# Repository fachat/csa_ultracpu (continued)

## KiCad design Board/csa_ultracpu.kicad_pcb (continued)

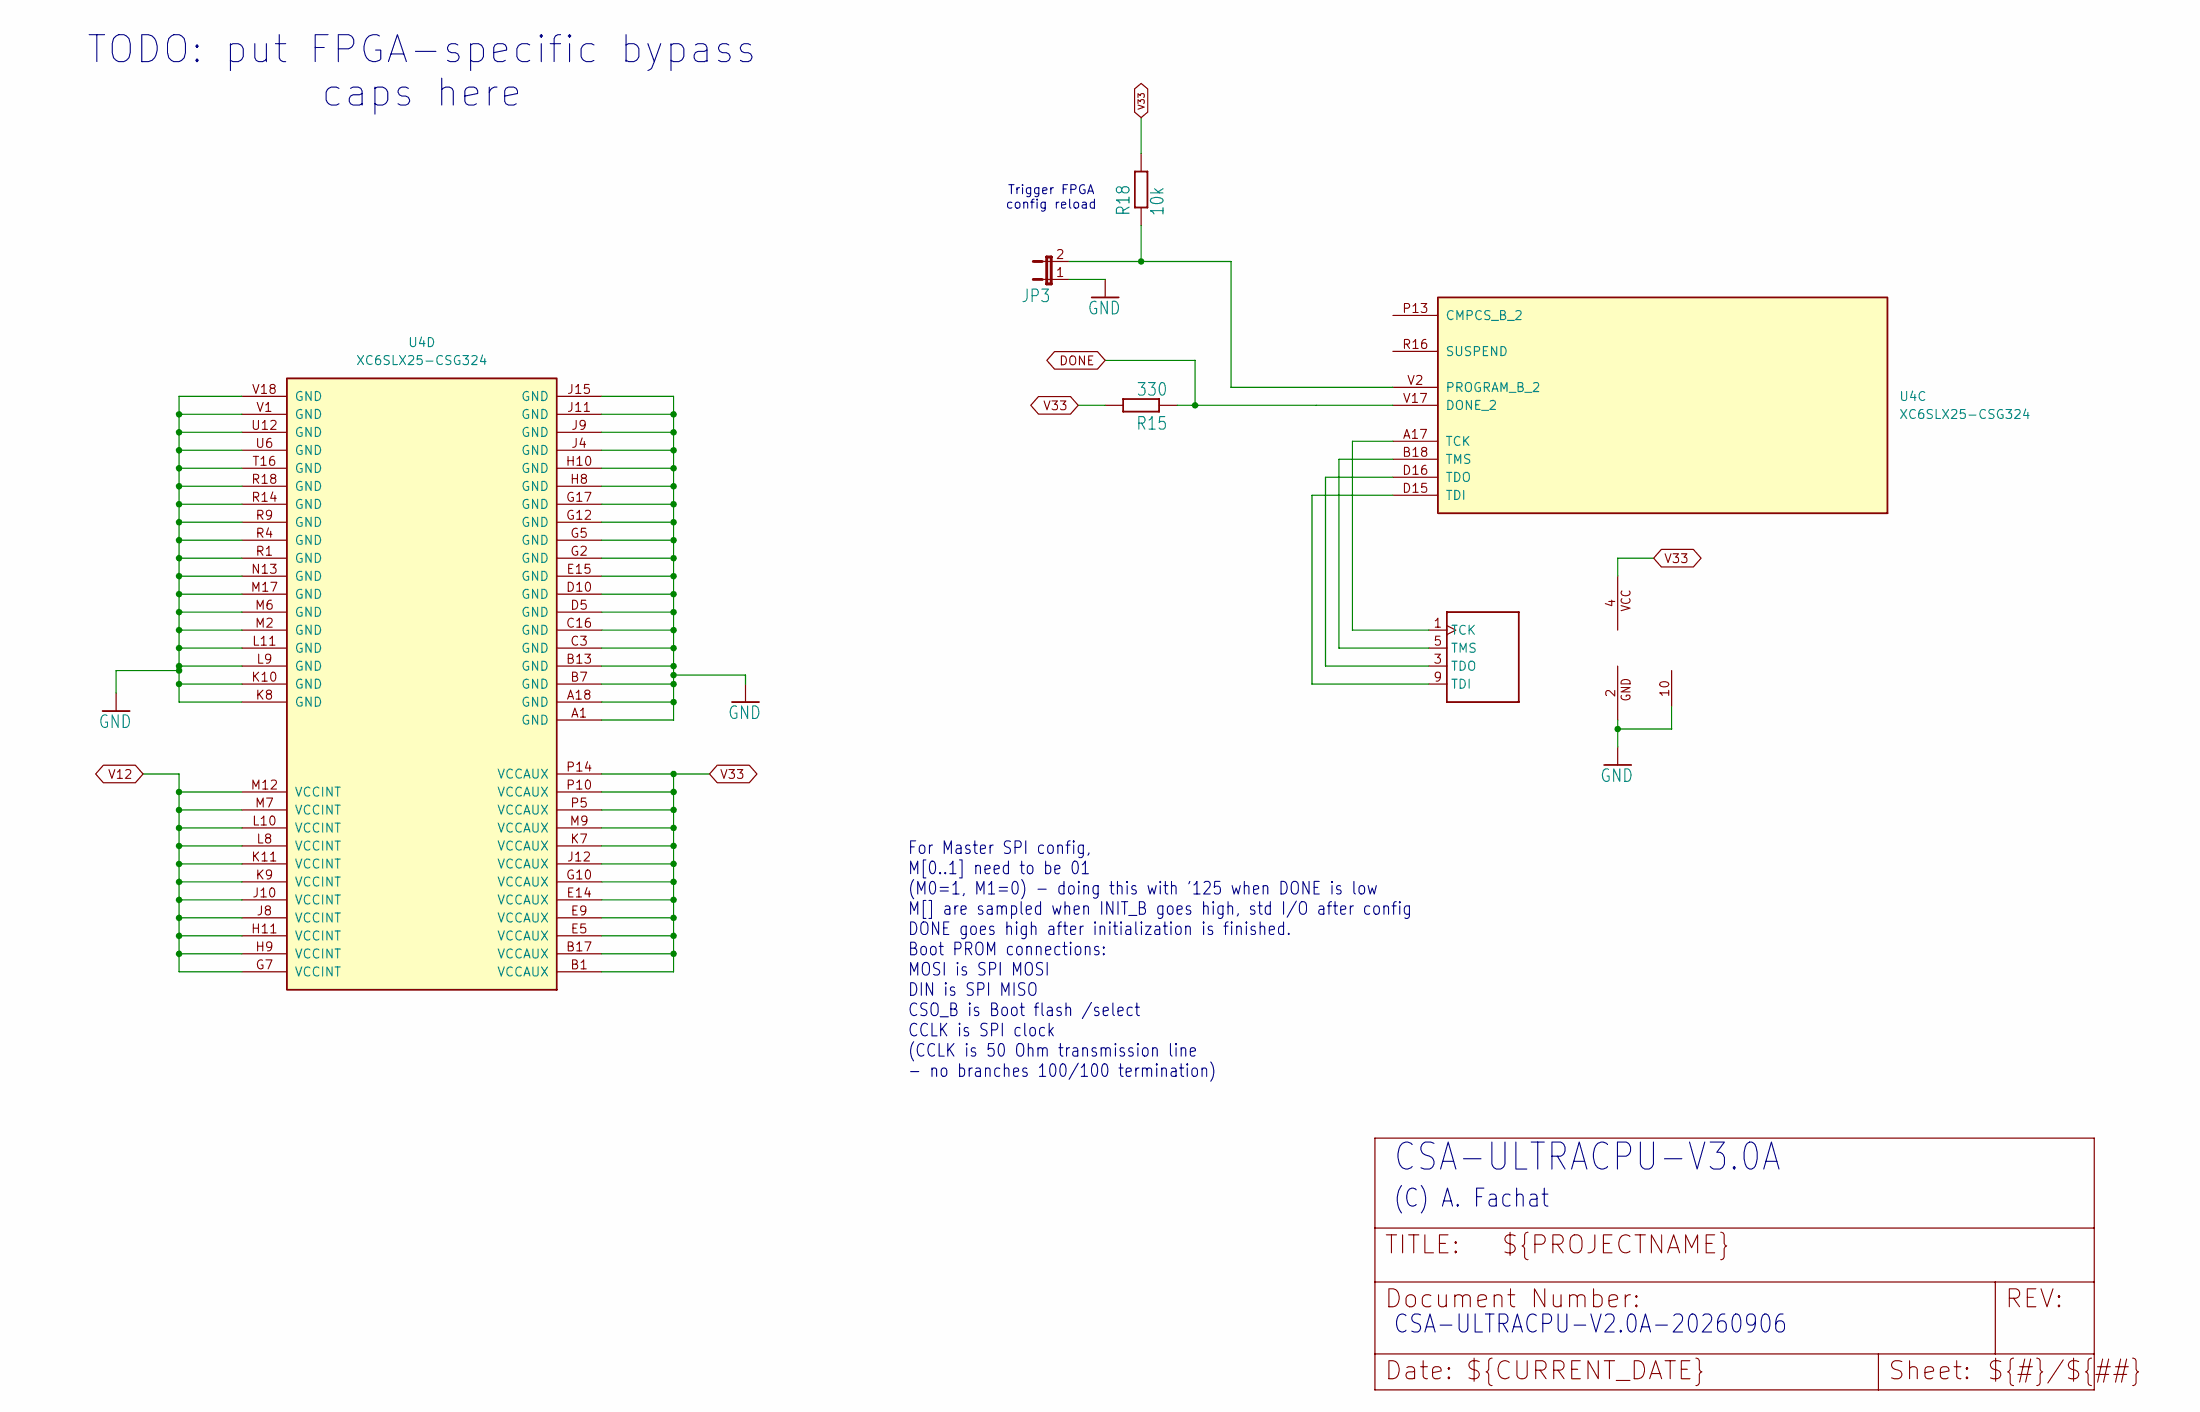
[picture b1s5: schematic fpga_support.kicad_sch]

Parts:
JP3: JP1E; JP1; LCSC C234182
R15: 330; C_0603_1608Metric_Pad1.08x0.95mm_HandSolder; LCSC C23138
R18: 10k; R_0805_2012Metric_Pad1.20x1.40mm_HandSolder; LCSC C17414
U4: XC6SLX25-CSG324; Xilinx_CSG324; LCSC C169795
U$2: XILINXPROG; FLAT10BOX; LCSC C5665

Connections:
DONE: R15.1, U4.V17 (DONE_2); also elsewhere on the board
GND: JP3.1, U4.A1 (GND), U4.A18 (GND), U4.B7 (GND), U4.B13 (GND), U4.C3 (GND), U4.C16 (GND), U4.D5 (GND), U4.D10 (GND), U4.E15 (GND), U4.G2 (GND), U4.G5 (GND), U4.G12 (GND), U4.G17 (GND), U4.H8 (GND), U4.H10 (GND), U4.J4 (GND), U4.J9 (GND), U4.J11 (GND), U4.J15 (GND), U4.K8 (GND), U4.K10 (GND), U4.L9 (GND), U4.L11 (GND), U4.M2 (GND), U4.M6 (GND), U4.M17 (GND), U4.N13 (GND), U4.R1 (GND), U4.R4 (GND), U4.R9 (GND), U4.R14 (GND), U4.R18 (GND), U4.T16 (GND), U4.U6 (GND), U4.U12 (GND), U4.V1 (GND), U4.V18 (GND), U$2.2 (GND), U$2.10; also elsewhere on the board
unnamed: JP3.2, R18.1, U4.V2 (PROGRAM_B_2)
unnamed: U4.A17 (TCK), U$2.1 (TCK)
unnamed: U4.D15 (TDI), U$2.9 (TDI)
unnamed: U4.D16 (TDO), U$2.3 (TDO)
unnamed: U4.B18 (TMS), U$2.5 (TMS)
V12: U4.G7 (VCCINT), U4.H9 (VCCINT), U4.H11 (VCCINT), U4.J8 (VCCINT), U4.J10 (VCCINT), U4.K9 (VCCINT), U4.K11 (VCCINT), U4.L8 (VCCINT), U4.L10 (VCCINT), U4.M7 (VCCINT), U4.M12 (VCCINT); also elsewhere on the board
V33: R15.2, R18.2, U4.B1 (VCCAUX), U4.B17 (VCCAUX), U4.E5 (VCCAUX), U4.E9 (VCCAUX), U4.E14 (VCCAUX), U4.G10 (VCCAUX), U4.J12 (VCCAUX), U4.K7 (VCCAUX), U4.M9 (VCCAUX), U4.P5 (VCCAUX), U4.P10 (VCCAUX), U4.P14 (VCCAUX), U$2.4 (VCC); also elsewhere on the board

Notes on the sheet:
For Master SPI config, M[0..1] need to be 01 (M0=1, M1=0) - doing this with '125 when DONE is low M[] are sampled when INIT_B goes high, std I/O after config DONE goes high after initialization is finished. Boot PROM connections: MOSI is SPI MOSI DIN is SPI MISO CSO_B is Boot flash /select CCLK is 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
CSA-ULTRACPU-V3.0A
TODO: put FPGA-specific bypass caps here
Trigger FPGA config reload
CSA-ULTRACPU-V2.0A-20260906
(C) A. Fachat

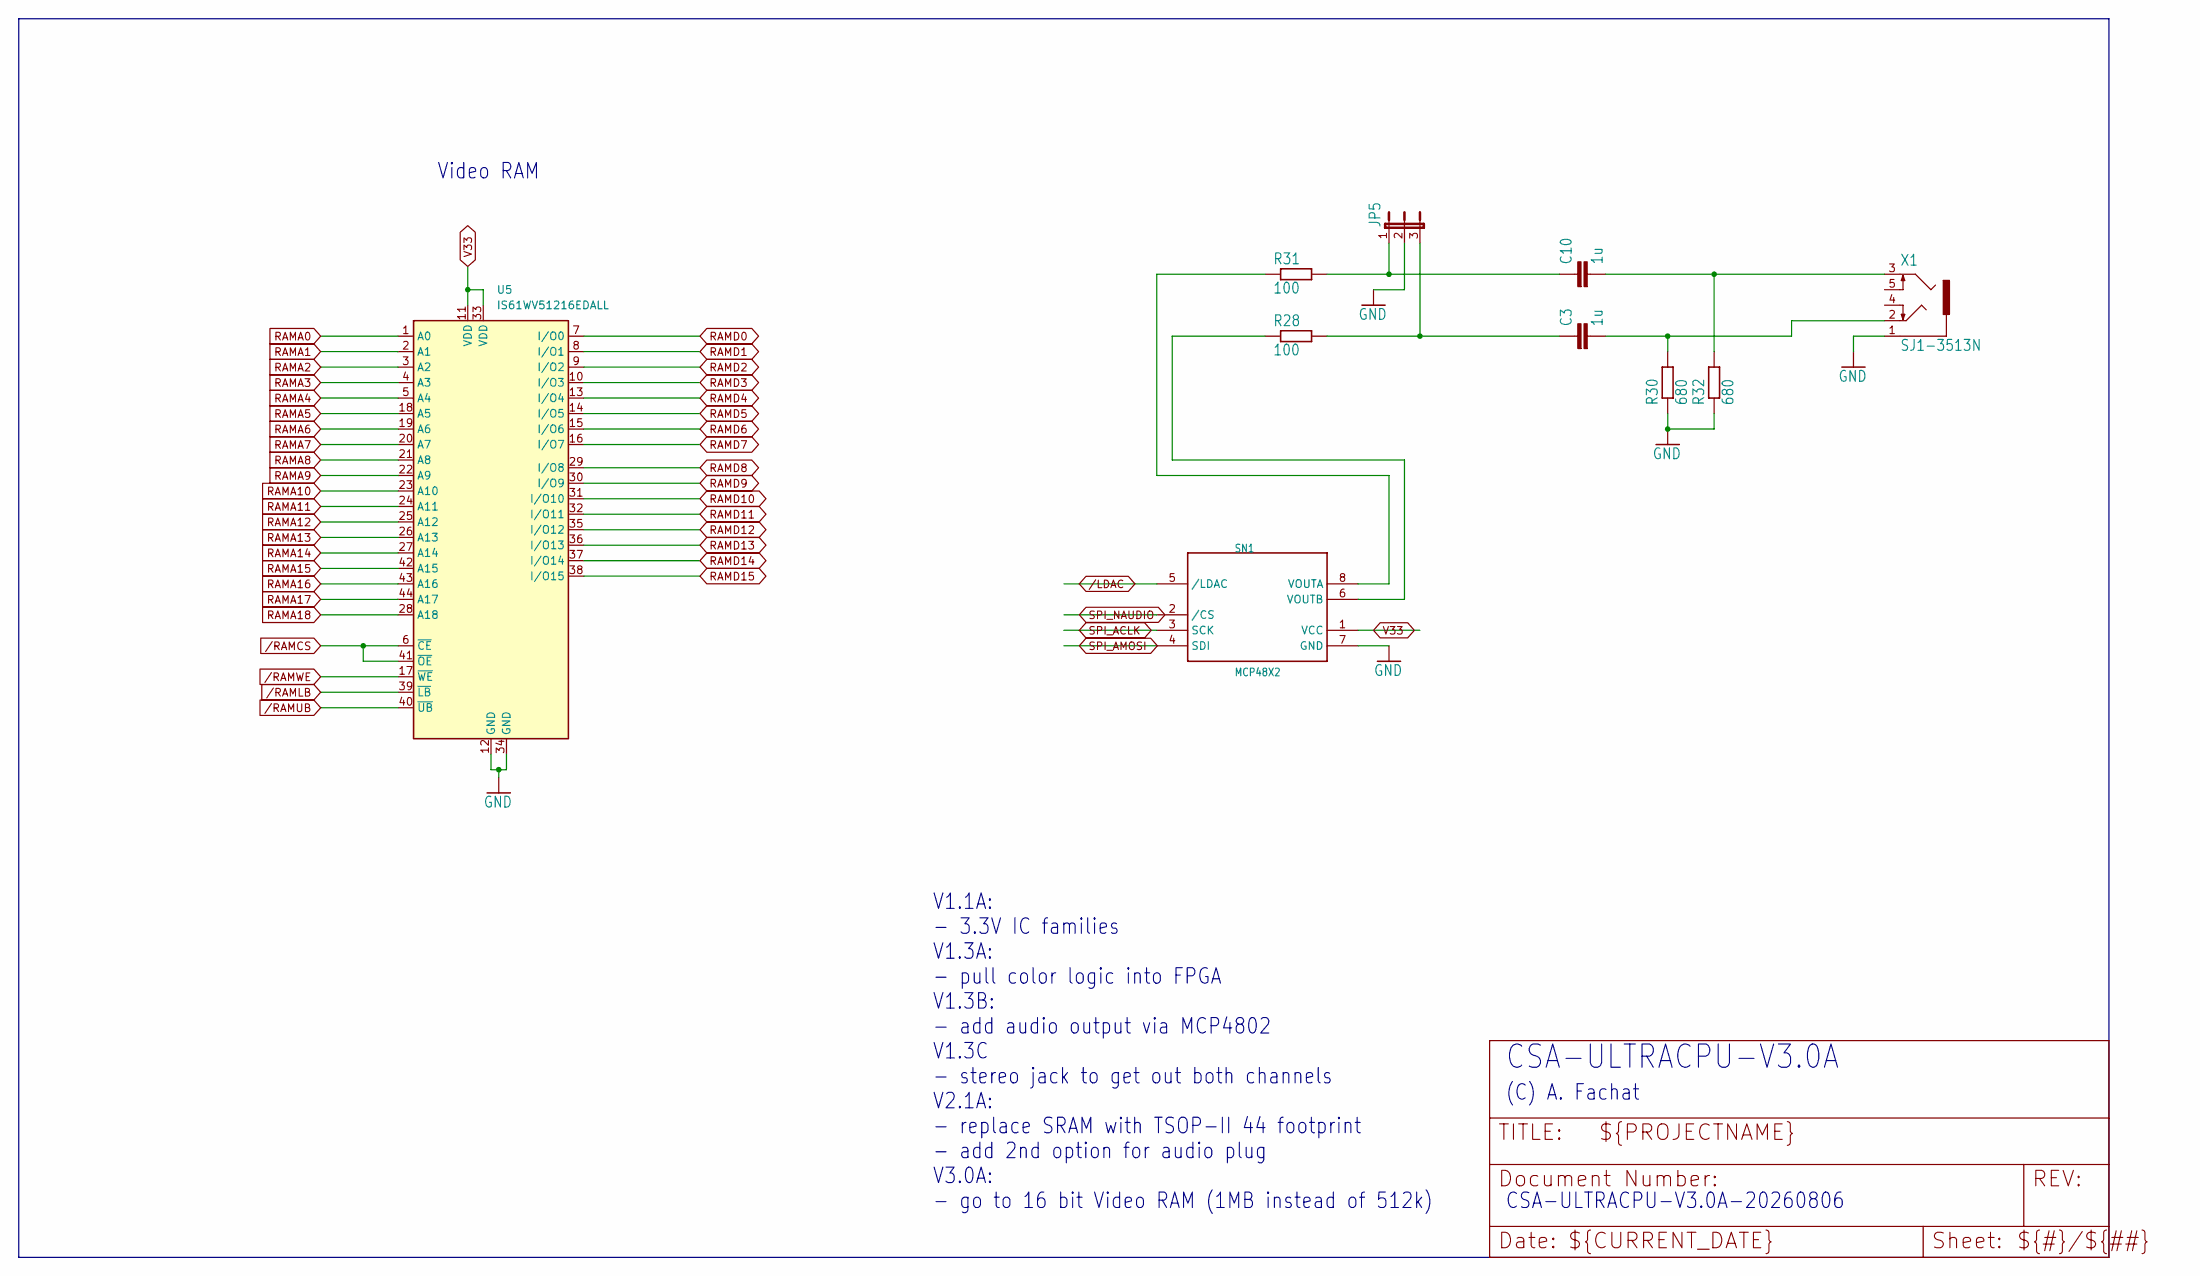
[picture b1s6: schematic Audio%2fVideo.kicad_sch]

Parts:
C3, C10: 1u; C_0603_1608Metric; LCSC C15849
JP5: JP2E; JP2; LCSC C587036
R28, R31: 100; R_0603_1608Metric_Pad0.98x0.95mm_HandSolder; LCSC C22775
R30, R32: 680; R_0603_1608Metric_Pad0.98x0.95mm_HandSolder; LCSC C23228
SN1: MCP48X2; SOIC8; LCSC C144363
U5: IS61WV51216EDALL; TSOP-II-44_10.16x18.41mm_P0.8mm; LCSC C57407
X1: SJ1-3513N; 1503_09; LCSC C145814

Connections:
GND: JP5.2, R30.1, R32.1, SN1.7 (GND), U5.12 (GND), U5.34 (GND), X1.1; also elsewhere on the board
unnamed: C3.1, JP5.3, R28.2
unnamed: C3.2, R30.2, X1.2
unnamed: C10.1, JP5.1, R31.2
unnamed: C10.2, R32.2, X1.3
unnamed: R31.1, SN1.8 (VOUTA)
unnamed: R28.1, SN1.6 (VOUTB)
RAMA0: U5.1 (A0); also elsewhere on the board
RAMA1: U5.2 (A1); also elsewhere on the board
RAMA2: U5.3 (A2); also elsewhere on the board
RAMA3: U5.4 (A3); also elsewhere on the board
RAMA4: U5.5 (A4); also elsewhere on the board
RAMA5: U5.18 (A5); also elsewhere on the board
RAMA6: U5.19 (A6); also elsewhere on the board
RAMA7: U5.20 (A7); also elsewhere on the board
RAMA8: U5.21 (A8); also elsewhere on the board
RAMA9: U5.22 (A9); also elsewhere on the board
RAMA10: U5.23 (A10); also elsewhere on the board
RAMA11: U5.24 (A11); also elsewhere on the board
RAMA12: U5.25 (A12); also elsewhere on the board
RAMA13: U5.26 (A13); also elsewhere on the board
RAMA14: U5.27 (A14); also elsewhere on the board
RAMA15: U5.42 (A15); also elsewhere on the board
RAMA16: U5.43 (A16); also elsewhere on the board
RAMA17: U5.44 (A17); also elsewhere on the board
RAMA18: U5.28 (A18); also elsewhere on the board
RAMD0: U5.7 (I/O0); also elsewhere on the board
RAMD1: U5.8 (I/O1); also elsewhere on the board
RAMD2: U5.9 (I/O2); also elsewhere on the board
RAMD3: U5.10 (I/O3); also elsewhere on the board
RAMD4: U5.13 (I/O4); also elsewhere on the board
RAMD5: U5.14 (I/O5); also elsewhere on the board
RAMD6: U5.15 (I/O6); also elsewhere on the board
RAMD7: U5.16 (I/O7); also elsewhere on the board
RAMD8: U5.29 (I/O8); also elsewhere on the board
RAMD9: U5.30 (I/O9); also elsewhere on the board
RAMD10: U5.31 (I/O10); also elsewhere on the board
RAMD11: U5.32 (I/O11); also elsewhere on the board
RAMD12: U5.35 (I/O12); also elsewhere on the board
RAMD13: U5.36 (I/O13); also elsewhere on the board
RAMD14: U5.37 (I/O14); also elsewhere on the board
RAMD15: U5.38 (I/O15); also elsewhere on the board
SPI_ACLK: SN1.3 (SCK); also elsewhere on the board
SPI_AMOSI: SN1.4 (SDI); also elsewhere on the board
SPI_NAUDIO: SN1.2 (/CS); also elsewhere on the board
V33: SN1.1 (VCC), U5.11 (VDD), U5.33 (VDD); also elsewhere on the board
/LDAC: SN1.5 (/LDAC); also elsewhere on the board
/RAMLB: U5.39 (~LB); also elsewhere on the board
/RAMUB: U5.40 (~UB); also elsewhere on the board

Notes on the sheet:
(C) A. Fachat
CSA-ULTRACPU-V3.0A-20260806
V1.1A: - 3.3V IC families V1.3A: - pull color logic into FPGA V1.3B: - add audio output via MCP4802 V1.3C - stereo jack to get out both channels V2.1A: - replace SRAM with TSOP-II 44 footprint - add 2nd option for audio plug V3.0A: - go to 16 bit Video RAM (1MB instead of 512k)
Video RAM
CSA-ULTRACPU-V3.0A

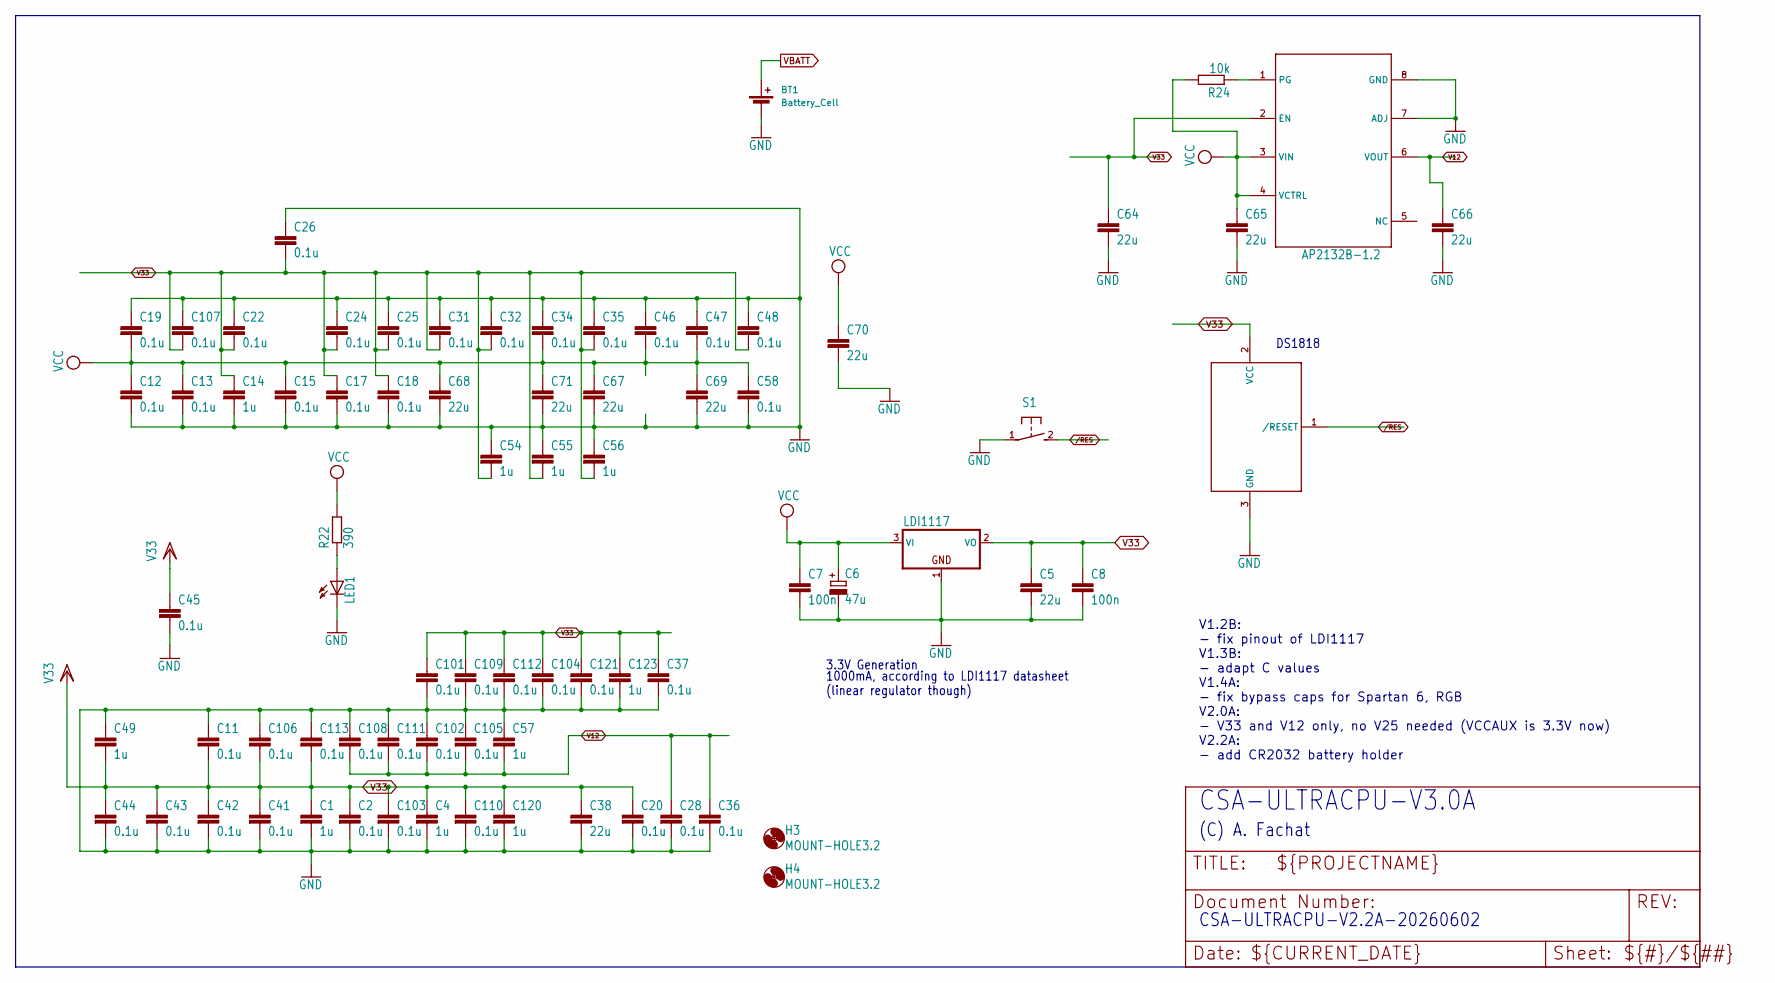
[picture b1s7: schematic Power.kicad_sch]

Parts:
BT1: Battery_Cell; Kinghelm CR2032 Holder; LCSC C5365915
C1, C4, C14, C49, C54, C55, C56, C57, C120, C123: 1u; C0603; LCSC C15849
C2, C11, C12, C13, C15, C17, C18, C19, C20, C22, C24, C25, C26, C28, C31, C32, C34, C35, C36, C37, C41, C42, C43, C44, C45, C46, C47, C48, C58, C101, C102, C103, C104, C105, C106, C107, C108, C109, C110, C111, C112, C113, C121: 0.1u; C0603; LCSC C14663
C5, C38, C64, C65, C66, C67, C68, C69, C70, C71: 22u; C0805; LCSC C45783
C6: 47u; C_0805_2012Metric_Pad1.18x1.45mm_HandSolder; LCSC C16780
C7, C8: 100n; C0603; LCSC C14663
DS1818: DS1818; SOT-23; LCSC C143298
H3, H4: MOUNT-HOLE3.2; 3,2
LED1: LED3MM; LCSC C85161
R22: 390; R_0603_1608Metric_Pad0.98x0.95mm_HandSolder; LCSC C23151
R24: 10k; R_0805_2012Metric_Pad1.20x1.40mm_HandSolder; LCSC C17414
S1: 31-XX; B3F-31XX; LCSC C231320
U$3: LDI1117; SOT223; LCSC C6186
U$16: AP2132B-1.2; PSOP-8-FIXED; LCSC C338874

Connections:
GND: BT1.2 (-), C1.2, C2.2, C4.2, C5.2, C6.2 (-), C7.2, C8.2, C11.1, C12.2, C13.2, C14.2, C15.2, C17.2, C18.2, C19.1, C20.2, C22.1, C24.1, C25.1, C26.1, C28.2, C31.1, C32.1, C34.1, C35.1, C36.2, C37.2, C38.2, C41.2, C42.2, C43.2, C44.2, C45.2, C46.1, C47.1, C48.1, C49.1, C54.1, C55.1, C56.1, C57.1, C58.2, C64.2, C65.2, C66.2, C67.2, C68.2, C69.2, C70.2, C71.2, C101.2, C102.1, C103.2, C104.2, C105.1, C106.1, C107.1, C108.1, C109.2, C110.2, C111.1, C112.2, C113.1, C120.2, C121.2, C123.2, DS1818.3 (GND), LED1.K (C), S1.1, U$3.1 (GND), U$16.7 (ADJ), U$16.8 (GND); also elsewhere on the board
unnamed: LED1.A, R22.1
unnamed: R24.1, U$16.1 (PG)
V12: C28.1, C36.1, C57.2, C66.1, C102.2, C105.2, C108.2, C111.2, U$16.6 (VOUT); also elsewhere on the board
V33: C1.1, C2.1, C4.1, C5.1, C8.1, C11.2, C14.1, C17.1, C18.1, C20.1, C22.2, C24.2, C25.2, C26.2, C31.2, C32.2, C35.2, C37.1, C38.1, C41.1, C42.1, C43.1, C44.1, C45.1, C48.2, C49.2, C54.2, C55.2, C56.2, C64.1, C101.1, C103.1, C104.1, C106.2, C107.2, C109.1, C110.1, C112.1, C113.2, C120.1, C121.1, C123.1, DS1818.2 (VCC), U$3.2 (VO), U$16.2 (EN); also elsewhere on the board
VBATT: BT1.1 (+); also elsewhere on the board
VCC: C6.1 (+), C7.1, C12.1, C13.1, C15.1, C19.2, C34.2, C46.2, C47.2, C58.1, C65.1, C67.1, C68.1, C69.1, C70.1, C71.1, R22.2, R24.2, U$3.3 (VI), U$16.3 (VIN), U$16.4 (VCTRL); also elsewhere on the board
/RES: DS1818.1 (/RESET), S1.2 (S); also elsewhere on the board

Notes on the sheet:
DS1818
(C) A. Fachat
CSA-ULTRACPU-V3.0A
1000mA, according to LDI1117 datasheet (linear regulator though)
CSA-ULTRACPU-V2.2A-20260602
3.3V Generation
V1.2B: - fix pinout of LDI1117 V1.3B: - adapt C values V1.4A: - fix bypass caps for Spartan 6, RGB V2.0A: - V33 and V12 only, no V25 needed (VCCAUX is 3.3V now) V2.2A: - add CR2032 battery holder

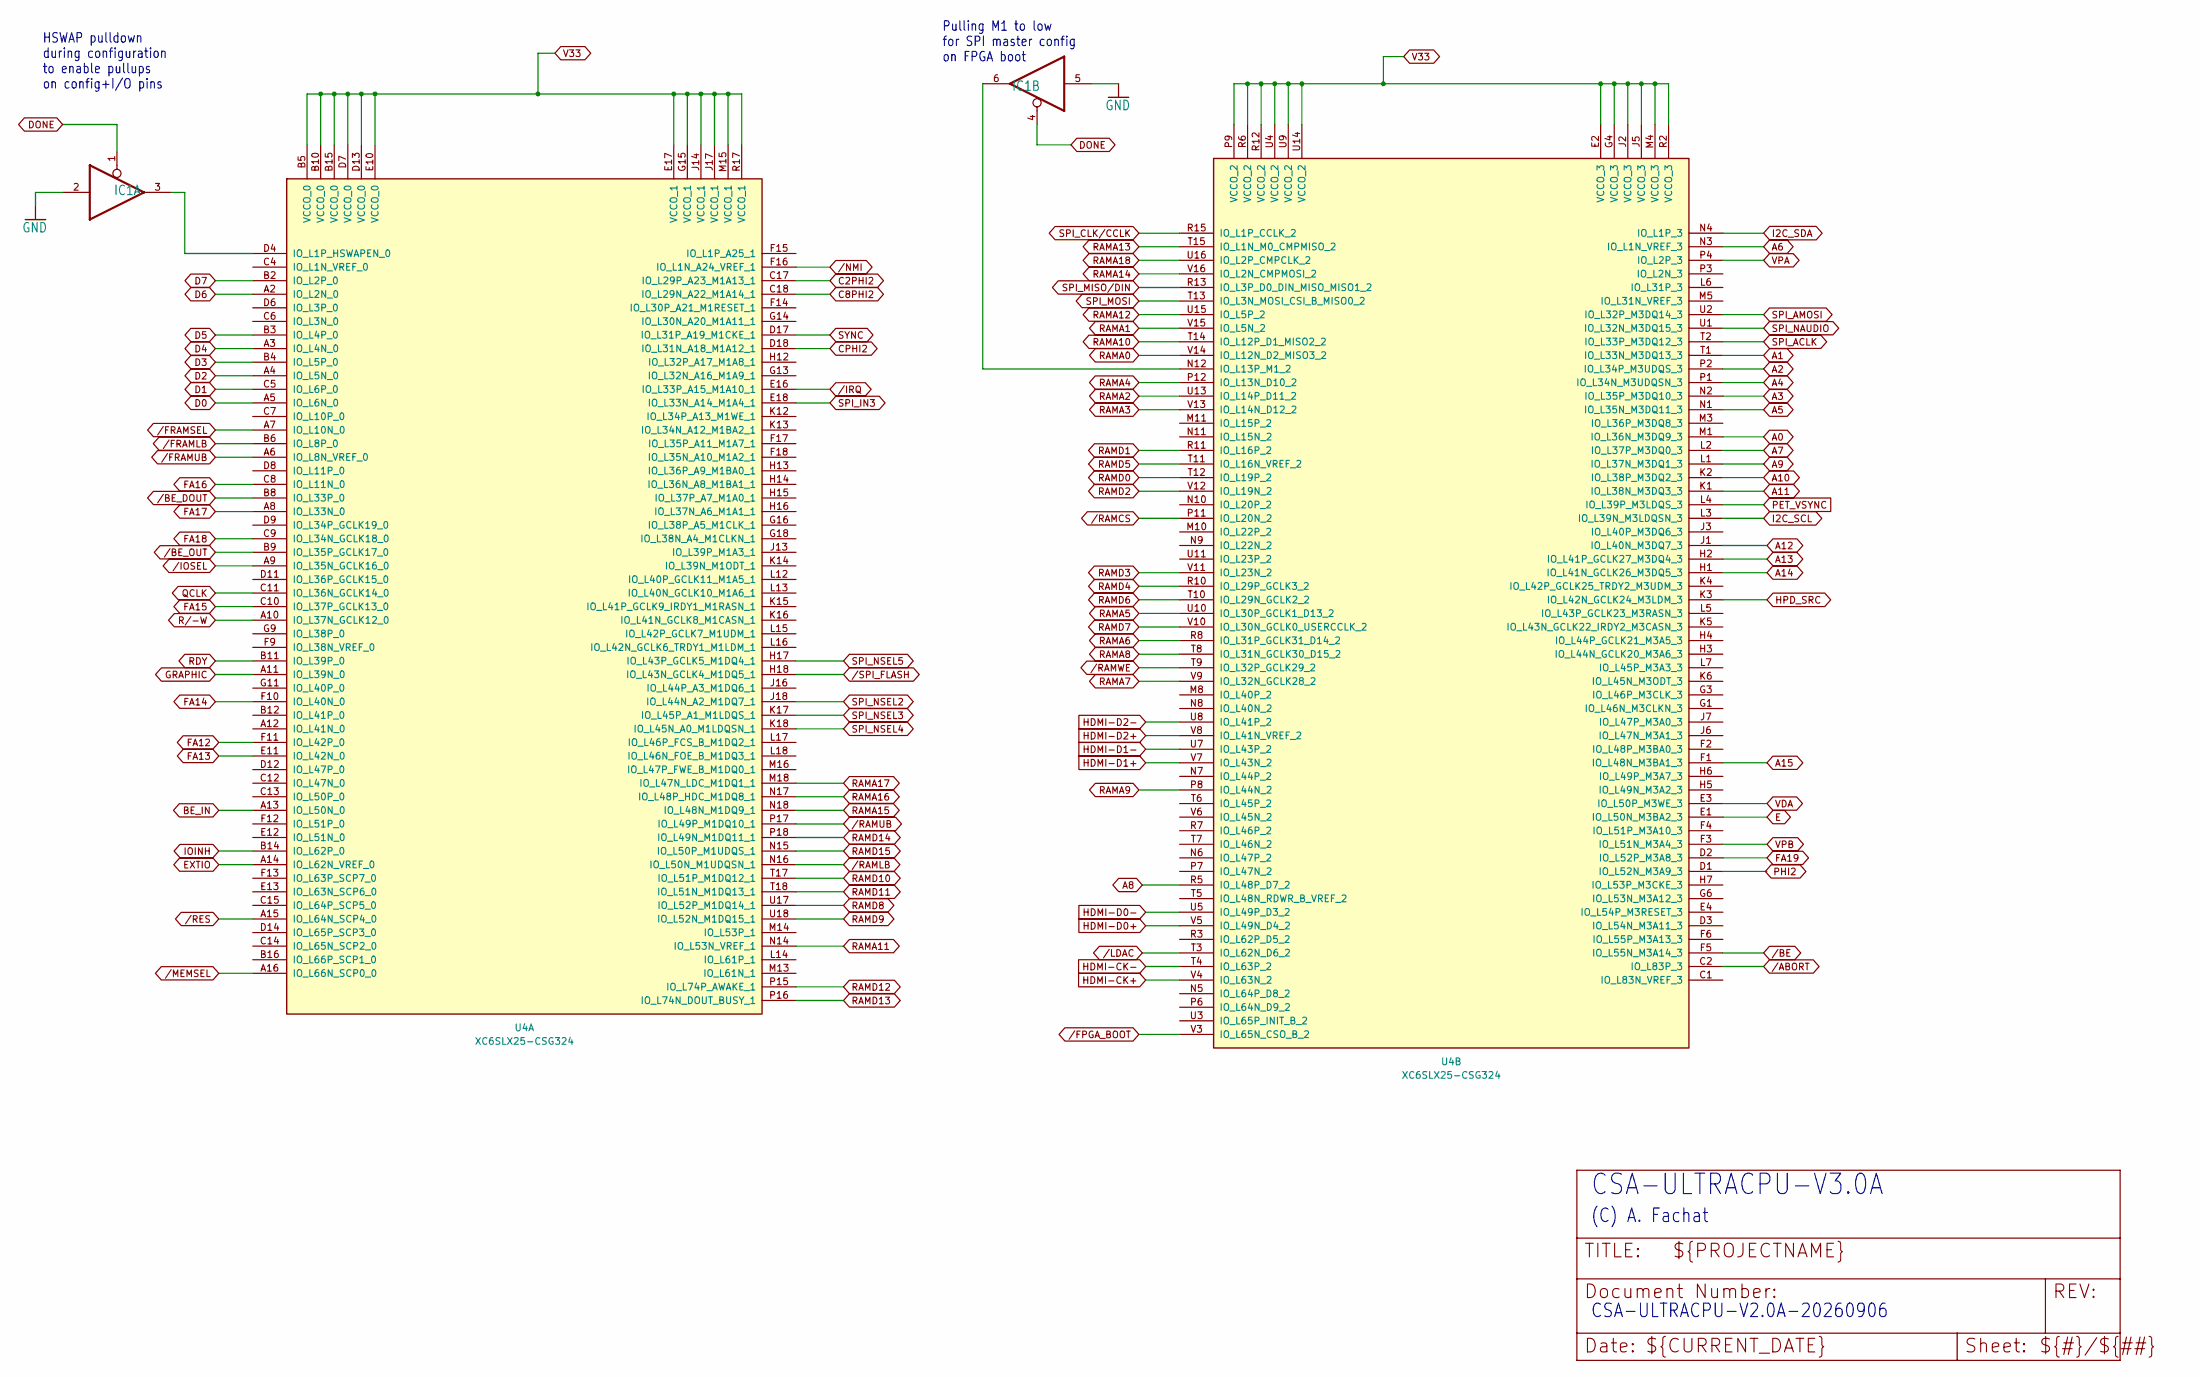
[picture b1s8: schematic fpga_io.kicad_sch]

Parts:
IC1: 74LVC125; SO14; LCSC C6057
U4: XC6SLX25-CSG324; Xilinx_CSG324; LCSC C169795

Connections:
A0: U4.M1 (IO_L36N_M3DQ9_3); also elsewhere on the board
A1: U4.T1 (IO_L33N_M3DQ13_3); also elsewhere on the board
A2: U4.P2 (IO_L34P_M3UDQS_3); also elsewhere on the board
A3: U4.N2 (IO_L35P_M3DQ10_3); also elsewhere on the board
A4: U4.P1 (IO_L34N_M3UDQSN_3); also elsewhere on the board
A5: U4.N1 (IO_L35N_M3DQ11_3); also elsewhere on the board
A6: U4.N3 (IO_L1N_VREF_3); also elsewhere on the board
A7: U4.L2 (IO_L37P_M3DQ0_3); also elsewhere on the board
A8: U4.R5 (IO_L48P_D7_2); also elsewhere on the board
A9: U4.L1 (IO_L37N_M3DQ1_3); also elsewhere on the board
A10: U4.K2 (IO_L38P_M3DQ2_3); also elsewhere on the board
A11: U4.K1 (IO_L38N_M3DQ3_3); also elsewhere on the board
A12: U4.J1 (IO_L40N_M3DQ7_3); also elsewhere on the board
A13: U4.H2 (IO_L41P_GCLK27_M3DQ4_3); also elsewhere on the board
A14: U4.H1 (IO_L41N_GCLK26_M3DQ5_3); also elsewhere on the board
A15: U4.F1 (IO_L48N_M3BA1_3); also elsewhere on the board
BE_IN: U4.A13 (IO_L50N_0); also elsewhere on the board
C2PHI2: U4.C17 (IO_L29P_A23_M1A13_1); also elsewhere on the board
C8PHI2: U4.C18 (IO_L29N_A22_M1A14_1); also elsewhere on the board
CPHI2: U4.D18 (IO_L31N_A18_M1A12_1); also elsewhere on the board
D0: U4.A5 (IO_L6N_0); also elsewhere on the board
D1: U4.C5 (IO_L6P_0); also elsewhere on the board
D2: U4.A4 (IO_L5N_0); also elsewhere on the board
D3: U4.B4 (IO_L5P_0); also elsewhere on the board
D4: U4.A3 (IO_L4N_0); also elsewhere on the board
D5: U4.B3 (IO_L4P_0); also elsewhere on the board
D6: U4.A2 (IO_L2N_0); also elsewhere on the board
D7: U4.B2 (IO_L2P_0); also elsewhere on the board
DONE: IC1.1 (OE), IC1.4 (OE); also elsewhere on the board
E: U4.E1 (IO_L50N_M3BA2_3); also elsewhere on the board
EXTIO: U4.A14 (IO_L62N_VREF_0); also elsewhere on the board
FA12: U4.F11 (IO_L42P_0); also elsewhere on the board
FA13: U4.E11 (IO_L42N_0); also elsewhere on the board
FA14: U4.F10 (IO_L40N_0); also elsewhere on the board
FA15: U4.C10 (IO_L37P_GCLK13_0); also elsewhere on the board
FA16: U4.C8 (IO_L11N_0); also elsewhere on the board
FA17: U4.A8 (IO_L33N_0); also elsewhere on the board
FA18: U4.C9 (IO_L34N_GCLK18_0); also elsewhere on the board
FA19: U4.D2 (IO_L52P_M3A8_3); also elsewhere on the board
GND: IC1.2 (I), IC1.5 (I); also elsewhere on the board
GRAPHIC: U4.A11 (IO_L39N_0); also elsewhere on the board
HDMI-CK+: U4.V4 (IO_L63N_2); also elsewhere on the board
HDMI-CK-: U4.T4 (IO_L63P_2); also elsewhere on the board
HDMI-D0+: U4.V5 (IO_L49N_D4_2); also elsewhere on the board
HDMI-D0-: U4.U5 (IO_L49P_D3_2); also elsewhere on the board
HDMI-D1+: U4.V7 (IO_L43N_2); also elsewhere on the board
HDMI-D1-: U4.U7 (IO_L43P_2); also elsewhere on the board
HDMI-D2+: U4.V8 (IO_L41N_VREF_2); also elsewhere on the board
HDMI-D2-: U4.U8 (IO_L41P_2); also elsewhere on the board
HPD_SRC: U4.K3 (IO_L42N_GCLK24_M3LDM_3); also elsewhere on the board
I2C_SCL: U4.L3 (IO_L39N_M3LDQSN_3); also elsewhere on the board
I2C_SDA: U4.N4 (IO_L1P_3); also elsewhere on the board
IOINH: U4.B14 (IO_L62P_0); also elsewhere on the board
unnamed: IC1.3 (O), U4.D4 (IO_L1P_HSWAPEN_0)
unnamed: IC1.6 (O), U4.N12 (IO_L13P_M1_2)
PET_VSYNC: U4.L4 (IO_L39P_M3LDQS_3); also elsewhere on the board
PHI2: U4.D1 (IO_L52N_M3A9_3); also elsewhere on the board
QCLK: U4.C11 (IO_L36N_GCLK14_0); also elsewhere on the board
RAMA0: U4.V14 (IO_L12N_D2_MISO3_2); also elsewhere on the board
RAMA1: U4.V15 (IO_L5N_2); also elsewhere on the board
RAMA2: U4.U13 (IO_L14P_D11_2); also elsewhere on the board
RAMA3: U4.V13 (IO_L14N_D12_2); also elsewhere on the board
RAMA4: U4.P12 (IO_L13N_D10_2); also elsewhere on the board
RAMA5: U4.U10 (IO_L30P_GCLK1_D13_2); also elsewhere on the board
RAMA6: U4.R8 (IO_L31P_GCLK31_D14_2); also elsewhere on the board
RAMA7: U4.V9 (IO_L32N_GCLK28_2); also elsewhere on the board
RAMA8: U4.T8 (IO_L31N_GCLK30_D15_2); also elsewhere on the board
RAMA9: U4.P8 (IO_L44N_2); also elsewhere on the board
RAMA10: U4.T14 (IO_L12P_D1_MISO2_2); also elsewhere on the board
RAMA11: U4.N14 (IO_L53N_VREF_1); also elsewhere on the board
RAMA12: U4.U15 (IO_L5P_2); also elsewhere on the board
RAMA13: U4.T15 (IO_L1N_M0_CMPMISO_2); also elsewhere on the board
RAMA14: U4.V16 (IO_L2N_CMPMOSI_2); also elsewhere on the board
RAMA15: U4.N18 (IO_L48N_M1DQ9_1); also elsewhere on the board
RAMA16: U4.N17 (IO_L48P_HDC_M1DQ8_1); also elsewhere on the board
RAMA17: U4.M18 (IO_L47N_LDC_M1DQ1_1); also elsewhere on the board
RAMA18: U4.U16 (IO_L2P_CMPCLK_2); also elsewhere on the board
RAMD0: U4.T12 (IO_L19P_2); also elsewhere on the board
RAMD1: U4.R11 (IO_L16P_2); also elsewhere on the board
RAMD2: U4.V12 (IO_L19N_2); also elsewhere on the board
RAMD3: U4.V11 (IO_L23N_2); also elsewhere on the board
RAMD4: U4.R10 (IO_L29P_GCLK3_2); also elsewhere on the board
RAMD5: U4.T11 (IO_L16N_VREF_2); also elsewhere on the board
RAMD6: U4.T10 (IO_L29N_GCLK2_2); also elsewhere on the board
RAMD7: U4.V10 (IO_L30N_GCLK0_USERCCLK_2); also elsewhere on the board
RAMD8: U4.U17 (IO_L52P_M1DQ14_1); also elsewhere on the board
RAMD9: U4.U18 (IO_L52N_M1DQ15_1); also elsewhere on the board
RAMD10: U4.T17 (IO_L51P_M1DQ12_1); also elsewhere on the board
RAMD11: U4.T18 (IO_L51N_M1DQ13_1); also elsewhere on the board
RAMD12: U4.P15 (IO_L74P_AWAKE_1); also elsewhere on the board
RAMD13: U4.P16 (IO_L74N_DOUT_BUSY_1); also elsewhere on the board
RAMD14: U4.P18 (IO_L49N_M1DQ11_1); also elsewhere on the board
RAMD15: U4.N15 (IO_L50P_M1UDQS_1); also elsewhere on the board
RDY: U4.B11 (IO_L39P_0); also elsewhere on the board
SPI_ACLK: U4.T2 (IO_L33P_M3DQ12_3); also elsewhere on the board
SPI_AMOSI: U4.U2 (IO_L32P_M3DQ14_3); also elsewhere on the board
SPI_CLK/CCLK: U4.R15 (IO_L1P_CCLK_2); also elsewhere on the board
SPI_IN3: U4.E18 (IO_L33N_A14_M1A4_1); also elsewhere on the board
SPI_MISO/DIN: U4.R13 (IO_L3P_D0_DIN_MISO_MISO1_2); also elsewhere on the board
SPI_MOSI: U4.T13 (IO_L3N_MOSI_CSI_B_MISO0_2); also elsewhere on the board
SPI_NAUDIO: U4.U1 (IO_L32N_M3DQ15_3); also elsewhere on the board
SPI_NSEL2: U4.J18 (IO_L44N_A2_M1DQ7_1); also elsewhere on the board
SPI_NSEL3: U4.K17 (IO_L45P_A1_M1LDQS_1); also elsewhere on the board
SPI_NSEL4: U4.K18 (IO_L45N_A0_M1LDQSN_1); also elsewhere on the board
SPI_NSEL5: U4.H17 (IO_L43P_GCLK5_M1DQ4_1); also elsewhere on the board
SYNC: U4.D17 (IO_L31P_A19_M1CKE_1); also elsewhere on the board
V33: U4.B5 (VCCO_0), U4.B10 (VCCO_0), U4.B15 (VCCO_0), U4.D7 (VCCO_0), U4.D13 (VCCO_0), U4.E2 (VCCO_3), U4.E10 (VCCO_0), U4.E17 (VCCO_1), U4.G4 (VCCO_3), U4.G15 (VCCO_1), U4.J2 (VCCO_3), U4.J5 (VCCO_3), U4.J14 (VCCO_1), U4.J17 (VCCO_1), U4.M4 (VCCO_3), U4.M15 (VCCO_1), U4.P9 (VCCO_2), U4.R2 (VCCO_3), U4.R6 (VCCO_2), U4.R12 (VCCO_2), U4.R17 (VCCO_1), U4.U4 (VCCO_2), U4.U9 (VCCO_2), U4.U14 (VCCO_2); also elsewhere on the board
VDA: U4.E3 (IO_L50P_M3WE_3); also elsewhere on the board
VPA: U4.P4 (IO_L2P_3); also elsewhere on the board
VPB: U4.F3 (IO_L51N_M3A4_3); also elsewhere on the board
/ABORT: U4.C2 (IO_L83P_3); also elsewhere on the board
/BE: U4.F5 (IO_L55N_M3A14_3); also elsewhere on the board
/BE_DOUT: U4.B8 (IO_L33P_0); also elsewhere on the board
/BE_OUT: U4.B9 (IO_L35P_GCLK17_0); also elsewhere on the board
/FPGA_BOOT: U4.V3 (IO_L65N_CSO_B_2); also elsewhere on the board
/FRAMLB: U4.B6 (IO_L8P_0); also elsewhere on the board
/FRAMSEL: U4.A7 (IO_L10N_0); also elsewhere on the board
/FRAMUB: U4.A6 (IO_L8N_VREF_0); also elsewhere on the board
/IOSEL: U4.A9 (IO_L35N_GCLK16_0); also elsewhere on the board
/IRQ: U4.E16 (IO_L33P_A15_M1A10_1); also elsewhere on the board
/LDAC: U4.T3 (IO_L62N_D6_2); also elsewhere on the board
/MEMSEL: U4.A16 (IO_L66N_SCP0_0); also elsewhere on the board
/RAMLB: U4.N16 (IO_L50N_M1UDQSN_1); also elsewhere on the board
/RAMUB: U4.P17 (IO_L49P_M1DQ10_1); also elsewhere on the board
/RES: U4.A15 (IO_L64N_SCP4_0); also elsewhere on the board
/SPI_FLASH: U4.H18 (IO_L43N_GCLK4_M1DQ5_1); also elsewhere on the board

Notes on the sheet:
HSWAP pulldown during configuration to enable pullups on config+I/O pins
CSA-ULTRACPU-V2.0A-20260906
Pulling M1 to low for SPI master config on FPGA boot
CSA-ULTRACPU-V3.0A
(C) A. Fachat

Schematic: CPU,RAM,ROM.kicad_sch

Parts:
IC1: 74LVC125; SO14; LCSC C6057
IC6: 741G04DBV; SOT23-5; LCSC C434067
JP7: JP4E; JP4; LCSC C587039
JP8, JP9, JP10, JP11: PIN
R3, R9, R10, R11: 10k; R_0805_2012Metric_Pad1.20x1.40mm_HandSolder; LCSC C17414
U1: IS61WV51216EDALL; TSOP-II-44_10.16x18.41mm_P0.8mm; LCSC C57407
U$1: W65C816SPLCC; PLCC44; LCSC C72279
U$4, U$18: SPIFLASH; DIL08; LCSC C72124
X3: SG-8002CE; Oscillator_SMD_SeikoEpson_SG8002CE-4Pin_3.2x2.5mm; LCSC C2831398

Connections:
/CPU,RAM,ROM/BE: IC6.4 (O), U$1.40 (BE)
/CPU,RAM,ROM/MLB: U$1.6 (MLB)
/CPU,RAM,ROM/M/X: U$1.42 (M/X)
A0: U1.25 (A12), U$1.10 (A0); also elsewhere on the board
A1: U1.26 (A13), U$1.11 (A1); also elsewhere on the board
A2: U1.27 (A14), U$1.13 (A2); also elsewhere on the board
A3: U1.28 (A18), U$1.14 (A3); also elsewhere on the board
A4: U1.5 (A4), U$1.15 (A4); also elsewhere on the board
A5: U1.18 (A5), U$1.16 (A5); also elsewhere on the board
A6: U1.19 (A6), U$1.17 (A6); also elsewhere on the board
A7: U1.20 (A7), U$1.18 (A7); also elsewhere on the board
A8: U1.21 (A8), U$1.19 (A8); also elsewhere on the board
A9: U1.22 (A9), U$1.20 (A9); also elsewhere on the board
A10: U1.23 (A10), U$1.21 (A10); also elsewhere on the board
A11: U1.24 (A11), U$1.22 (A11); also elsewhere on the board
A12: U$1.25 (A12); also elsewhere on the board
A13: U$1.26 (A13); also elsewhere on the board
A14: U$1.27 (A14); also elsewhere on the board
A15: U$1.28 (A15); also elsewhere on the board
D0: U1.7 (I/O0), U1.38 (I/O15), U$1.36 (D0/BA0); also elsewhere on the board
D1: U1.8 (I/O1), U1.37 (I/O14), U$1.35 (D1/BA1); also elsewhere on the board
D2: U1.9 (I/O2), U1.36 (I/O13), U$1.34 (D2/BA2); also elsewhere on the board
D3: U1.10 (I/O3), U1.35 (I/O12), U$1.33 (D3/BA3); also elsewhere on the board
D4: U1.13 (I/O4), U1.32 (I/O11), U$1.32 (D4/BA4); also elsewhere on the board
D5: U1.14 (I/O5), U1.31 (I/O10), U$1.31 (D5/BA5); also elsewhere on the board
D6: U1.15 (I/O6), U1.30 (I/O9), U$1.30 (D6/BA6); also elsewhere on the board
D7: U1.16 (I/O7), U1.29 (I/O8), U$1.29 (D7/BA7); also elsewhere on the board
DONE: IC1.10 (OE); also elsewhere on the board
E: U$1.39 (E); also elsewhere on the board
FA12: U1.1 (A0); also elsewhere on the board
FA13: U1.2 (A1); also elsewhere on the board
FA14: U1.3 (A2); also elsewhere on the board
FA15: U1.4 (A3); also elsewhere on the board
FA16: U1.43 (A16); also elsewhere on the board
FA17: U1.44 (A17); also elsewhere on the board
FA18: U1.42 (A15); also elsewhere on the board
GND: IC1.7 (GND), IC1.9 (I), IC6.3 (GND), JP7.3, U1.12 (GND), U1.34 (GND), U$1.1, U$1.23 (VSS), U$1.24 (GND), U$4.4 (GND), U$18.4 (GND), X3.2 (GND); also elsewhere on the board
unnamed: R3.2, X3.1 (OE)
PHI2: JP9.1 (1_1), U$1.41 (PH2-IN); also elsewhere on the board
QCLK: X3.3 (OUT); also elsewhere on the board
RDY: U$1.3 (RDY); also elsewhere on the board
SPI_CLK/CCLK: U$4.6 (SCK), U$18.6 (SCK); also elsewhere on the board
SPI_MISO/DIN: U$4.2 (SO), U$18.2 (SO); also elsewhere on the board
SPI_MOSI: U$4.5 (SI), U$18.5 (SI); also elsewhere on the board
V33: IC1.14 (VCC), IC6.5 (VCC), R3.1, R9.1, R10.1, R11.1, U1.11 (VDD), U1.33 (VDD), U$1.9 (VCC), U$1.37 (VDD), U$4.7 (/HOLD), U$4.8 (VCC), U$18.7 (/HOLD), U$18.8 (VCC), X3.4 (Vcc); also elsewhere on the board
VDA: U$1.43 (VDA); also elsewhere on the board
VPA: U$1.8 (VPA); also elsewhere on the board
VPB: JP8.1 (1_1), U$1.2 (VPB); also elsewhere on the board
/ABORT: JP7.2, R10.2, U$1.4 (ABORTB); also elsewhere on the board
/BE: IC6.2 (I); also elsewhere on the board
/FPGA_BOOT: U$18.1 (/CS); also elsewhere on the board
/FRAMLB: U1.39 (~LB); also elsewhere on the board
/FRAMSEL: U1.6 (~CE), U1.41 (~OE); also elsewhere on the board
/FRAMUB: U1.40 (~UB); also elsewhere on the board
/IRQ: JP11.1 (1_1), R9.2, U$1.5 (IRQB); also elsewhere on the board
/RES: IC1.8 (O), JP7.1, U$1.44 (RESB); also elsewhere on the board
/SPI_FLASH: JP10.1 (1_1), U$4.1 (/CS); also elsewhere on the board

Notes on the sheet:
PHI2 test point
/NFLASH (boot) test point
Address line ordering to facilitate better PCB routing: FPGA only Ax on "upper" half of chip.
CSA-ULTRACPU-V3.0A-20260905
CSA-UTRACPU-V3.0A
Fast RAM
V2.0A: - use CCLK for all SPI clocks - add switchable CPU BE input - VCCAUX is 3.3V now - Added test points V2.0B: - IC6 power supply to 3.3V instead of 5V - Pulldown /RES as long as DONE is low V2.1A: - use TSOP-II 44 pin package for SRAM - use 3225 package for 54MHz SMD oscillator V3.0A: - go fro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
VPB test point
(C) A. Fachat

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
